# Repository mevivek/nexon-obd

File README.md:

# Obdurate

> *ob·du·rate* — adj. unyielding; refusing to be moved.

**A read-only black box for your car.** It plugs into the OBD-II port and stays
there. It records every drive to onboard flash whether or not a phone is connected,
prints the sample rate it is actually achieving next to every reading, and never
writes anything to the car — which is a test, not a promise: the build fails if a
write service ever appears in the source.

Built on a **Seeed XIAO ESP32S3**. It hosts its own Wi-Fi access point and serves a
gauge dashboard, on-board monitor results, a UDS identifier scanner and browser-based
OTA updates. No app, no account, no internet, no cloud. Join its Wi-Fi and a page
opens; don't, and it keeps recording anyway.

**Developed and verified against a 2022 Tata Nexon 1.2 petrol (BS6).** The transport
layer, ISO-TP, the recorder, the scanner and the honesty rules are generic. The PID
lists (`PID_B1`–`PID_B4`), the ECU addresses (`ID_ECM_REQ`/`ID_TCM_REQ`), the bus
timing and the warning thresholds are that car's — a different one needs those
changed in the source, and there is no porting guide yet. If you try it on another
car, the measurements are the interesting part; open an issue.

[`docs/FINDINGS.md`](docs/FINDINGS.md) is what was measured on this one, including a
catalogue of the ways a cheap ELM327 clone lies to you.

It reaches the car two ways and picks whichever works:

| Transport | Hardware | Speed | Notes |
|---|---|---|---|
| **BLE ELM327** | none — uses a dual-mode ELM327 already in the OBD port | ~2 Hz | Works today |
| **Direct CAN** | SN65HVD230 transceiver (~₹200) | 50–100 Hz | Preferred once wired |

Everything here was verified against the actual vehicle. Where a claim is untested,
it says so.

---

## Quick start

1. Flash the firmware (see [Building](#building)).
2. Power the board — USB, or from the OBD port via a 12 V→5 V buck.
3. Join Wi-Fi **`Obdurate`** / **`changeme1234`**.
4. Open **`http://192.168.4.1`**.

That is the whole install. The dashboard is compiled into the firmware, so flashing
is all it takes — there is no second step, no laptop at the car, and no state where
the board is running but has no page to show.

You can still deploy a bundle to the filesystem with **`web/deploy.sh`**, and it
takes precedence when present. That is the edit loop: changing a line of CSS costs a
22 KB upload rather than a 1.3 MB reflash. The compiled-in copy is the floor
underneath it, so a failed or half-finished deploy falls back to the last dashboard
that was built into the firmware rather than to a stub.

| Page | What it does |
|---|---|
| `/` | Live gauges — RPM, boost, temps, trims, lambda, catalyst, driver demand |
| `/monitors` | Mode 06 on-board monitor test results, with the ECU's own limits |
| `/scan` | Discover — the autopilot, the sweep, triage and the DID watch |
| `/update` | Upload a new `.bin` over Wi-Fi |
| `/dtc` | Stored + pending fault codes as JSON |
| `/data` | Current sample as JSON, plus firmware version and active transport |
| `/trips` | Per-drive CSV logs — list, download, delete |
| `/history` | The stored trend buffer as JSON |
| `/vehicle` | What this car is and which readings it supports, as JSON |
| `/car` | Which car this board is bound to, and whether it is recording |
| `/auto` | The autopilot's phase and progress |
| `/files` | What data is on the filesystem — the list a backup is built from |
| `/file` | One data file, streamed |
| `/reset` | Erase the data, or the data and the dashboard bundle |

The header shows the running firmware version and which transport is actually live
(`can` or `ble`), so a flashed image can be confirmed at a glance.

A poll can come back with only some of its PIDs — the dashboard reads them in three
batched requests, and one batch can time out while the others answer. When that
happens the affected gauges keep showing their last reading, dimmed, and the header
reports `live · holding N`. After 2.5 s without a fresh value they fall back to `—`
rather than showing stale data indefinitely, and a held reading never raises or
sustains a warning — a value from two seconds ago cannot tell you whether the engine
is still overheating.

A single dropped poll is not reported as a fault either — the status only changes to
`no response from ECU` after five consecutive failures. Dropped replies happen, the
values are held through them, and flipping the status on each one reads as a problem
when nothing is wrong.

### Polling runs on the board, not on the page

The board samples the ECU continuously in `loop()`, one batched request per turn,
and `/data` returns the newest cached sample rather than going to the bus. Polling
therefore does not stop when you close the browser, and no request ever waits for a
poll of its own.

It did, however, wait for *someone else's*. The web server is single threaded, and
until v1.8.0 it got exactly one turn per bus exchange — up to 1.2 s on BLE, twice
that when a batch is retried. A tab switch is three requests (the document, `/time`,
and the new page's first poll), so switching pages could sit behind several seconds
of ELM327 timeouts and felt like a page load rather than a page swap.

Two things fix that, both in `bus_yield.h`:

- **The wait loops serve HTTP.** Waiting on the car is otherwise `delay(1)` on BLE
  and a 5 ms blocking receive on CAN. Both now call `webYield()` instead, which
  serves whatever is queued and reports how long it took — and the response deadline
  moves out by exactly that, because the reply is still waiting behind us either way
  (the TWAI RX queue, or the ELM notify buffer). Without the give-back, serving a
  page would eat the ECU's patience window and surface as a phantom timeout. The
  extension is capped at 3 s so one slow handler cannot hold an exchange open.
- **`loop()` drains the queue** instead of taking one request per turn, so a whole
  page load completes in a single turn.

Two guards keep that safe. `WebServer` tracks a single current client, so
`webYield()` refuses to re-enter it from inside a handler; and `obdIsoTp()` sets a
flag for the duration of an exchange so a handler reached from a yield cannot start
a second one underneath a half-finished reassembly. `/dtc` is the only handler that
touches the bus — it stands down when that flag is set, and because it runs inside
`handleClient()` and therefore cannot yield, its own timeouts are kept short.

The pages help too: the shared ~7 KB stylesheet used to be compiled into all five
documents and re-sent on every switch. It is now served once from `/ui.css` with a
version-stamped, immutable URL, and the pages carry an `ETag` so a re-visit is a
304 with no body. That is also worth ~26 KB of flash.

A sample is published after **every** batch, not after all three. The other two are
carried forward from cache while they are still fresh (3 s), so the page updates at
the bus transaction rate rather than a third of it. Batches are not polled equally
either — `b1` carries everything with a sparkline (rpm, speed, MAP, throttle, load,
coolant) and gets half the turns, because oil temperature and battery voltage do not
move fast enough to deserve equal billing:

| | Refresh |
|---|---|
| `b1` — rpm, speed, MAP, throttle, load, coolant | every 3 batches |
| `b4` — pedal, commanded throttle, torque, absolute load | every 3 batches |
| `b2` — oil, IAT, voltage, trims, fuel rate | every 6 batches |
| `b3` — lambda, catalyst, timing, run time, ambient, fuel | every 6 batches |

A batch that has not answered for three of its own polling cycles is dropped to
`null` rather than published as current, so carrying values forward can never
present a stale number as live. That window is measured, not fixed: `b2` and `b3`
come round once every four batches, so a flat timeout only holds if a batch
completes quickly. Over BLE it does not, and those two batches then expire before
their next turn — blanking twelve of the twenty rows in **All values** on every
cycle. The dashboard's own hold window scales the same way, off the observed sample
interval.

The `[alive]` serial line prints `batch=`, `cycle=` and `stale=` so all three are
visible rather than inferred.

### The board says how fast it is actually reading the car

Those numbers used to go only to the serial log, where nobody sitting in a car can
read them. They are now in `/data` as a `q` block, and on the page as the muted
trailer next to the status pill:

```
live · holding 2      1.87 Hz · b3 6.8 s
```

The rate quoted is **the board's**, not the page's. The page's fetch loop is capped
by its poll interval and throttled harder still in a backgrounded tab, so a rate
measured there can only ever be at or below the one the board is publishing — it
would understate a healthy link and could never catch a sick one. Where the two
genuinely disagree, both are shown, because that is the case worth knowing about:
the log holds samples the screen is not showing you.

This is the number every tool in this category leaves out. An ELM327 round trip puts
a cheap clone somewhere near five PIDs a second; set a tenth-of-a-second logging
interval against that and you get a log that looks complete and is mostly the
previous row repeated, with nothing anywhere to tell you which it is.

Two rules keep it honest, and they are the same ones the readings themselves follow:

- **`hz` is null, not zero, until a full pass has been timed.** A rate of zero is a
  claim that the bus is dead. Not having measured one yet is not that claim, and the
  first second of every drive is spent in that state.
- **A batch that has never answered is null, not a very large age.** Never-answered
  is usually a PID this ECU does not support; long-ago-answered is a link going bad.
  Collapsing them presents the first as the second.

The stalest batch is named only once it is past the board's own derived staleness
window — `b2` and `b3` come round once every four turns by design, so reporting the
worst one unconditionally would be a permanent complaint about nothing.

`/data` also carries a `boot` block: how this run started (`power`, `wake`, `panic`,
`brownout`, `wdt`, …), how long it has been going, and how many deep-sleep wakes
since the last cold boot. A recorder that runs unattended has to be able to answer
*what happened while I was not looking* — a board that has quietly panicked and
restarted forty times otherwise looks exactly like one that has been up all week.

**On BLE, the bus transaction rate is the limit**, and it is mostly round-trip
latency rather than the ECU. The connection interval is the floor: at a default of
40–50 ms a request and its reply cannot beat about a tenth of a second however fast
the car answers. The firmware asks for 7.5–15 ms and a 247-byte MTU, which collapses
a ~80-character reply from four or five notifications into one or two. The adapter
may refuse either, in which case nothing is worse than before. The serial log prints
`batch=NNNms` so the real cost is visible rather than guessed at.

The dashboard stops requesting while the page is off screen, and the Hz readout
counts *published samples* rather than fetches — the same cached sample can be
fetched several times and must not inflate the rate.

### Mileage

Two figures, in the glance area under boost and coolant:

- **Mileage** — the average over this drive, with the totals it came from
  (`23.6 km · 1.66 L`) underneath so the number can be checked rather than trusted.
- **Right now** — instantaneous km/L, which is what the pedal moves. Standing still
  it reads `—` and says `idling` instead, because speed ÷ nothing is not a mileage.

There is no PID for fuel economy, so it is integrated on the board from speed
(`0D`) and fuel rate (`5E`), both confirmed supported on this ECU. On the board and
not on the page, so locking the phone or closing the browser does not lose the drive.
Two rules keep it honest:

- **Both inputs or neither.** Fuel rate lives in the `b2` batch and refreshes half as
  often as speed, so it goes absent regularly. Counting the distance anyway would
  divide real kilometres by an understated litre count and report a mileage better
  than the car achieved.
- **Gaps are not driving.** An interval longer than 5 s — a BLE dropout, a scan taking
  the bus, a wake from sleep — is skipped rather than integrated at the last known
  speed. The clock still moves, so the interval after an outage is one interval, not
  the whole outage.

The average is withheld until roughly the first 0.5 km and 0.1 L. Before that it
swings by tens of km/L between polls and reads as a broken gauge.

Totals start at zero each time the board powers up, which — given the
accessory-socket supply — is exactly one drive. They also go into the trip CSV as
`trip_km` and `trip_l`, so economy over any stretch of a drive can be recovered by
differencing two rows.

One caveat worth knowing: `5E` is the ECU's injection model, not a flow meter. Trip
km/L from it typically reads a few percent optimistic against tank-to-tank. It is
excellent for comparing drives and weaker as an absolute.

### Driver demand vs. delivery

Six of the 55 PIDs the ECM supports trace one chain: **accelerator pedal (`49`/`4A`)
→ commanded throttle (`4C`) → actual throttle (`11`) → demanded torque (`61`) →
delivered torque (`62`)**, with absolute load (`43`) alongside. That is what you
asked the car for, what the ECU decided to do about it, and what the engine actually
produced — which on a small turbo is the interesting part.

Torque is reported as a percentage of the engine's reference torque (`63`), a
constant read once at startup like barometric pressure, so the newton-metre figures
are derived rather than read.

> The scalings are the J1979 ones and have **not been verified against this car** —
> `FINDINGS.md` lists the torque PID scaling as an open question precisely because it
> needs data under load. A wrong data *length* is caught (`mode01Walk` rejects the
> batch), but a wrong *scaling* would not be. Treat the numbers as provisional until
> they have been watched under load and found sane.

### On-board monitors (mode 06)

Mode 06 is the ECU's own test results: what each monitor measured, and the limits it
is judged against. `FINDINGS.md` recorded it as supported (`46 00 C0000001`) and
never explored — so `/monitors` reads it.

The value of it over `/dtc` is that a fault code only appears once a system has
already failed. Mode 06 shows how much room is left, so a catalyst drifting toward
its threshold is visible while it is still passing.

**Pass and headroom do not require knowing the units.** A test passes when its value
sits inside its own limits, and the headroom is a fraction of that window — both
unit-free. The unit-and-scaling table is long and only partly documented, so values
are shown raw with their scaling id, decoded only where the multiplier is
unambiguous. Monitor names likewise: only unambiguous J1979 ids are named, the rest
keep their raw id rather than being given a label that might be wrong.

Discovery walks the support masks (`00` → `20` → `40` …, each mask's last bit
pointing at the next), then each monitor is read one at a time. It runs only while
the page is open — monitors move over minutes, and polling them continuously would
take bus time from the values that move now.

### The DID scan runs in the background

A scan is driven by the board, so it continues if you navigate away, close the
browser, or lock the phone. Only **Stop** — or an OTA upload, which never flashes
mid-scan — ends it.

While it runs the scanner takes most of the bus, but not all of it — the sampler
still gets one batch every two seconds, so live values keep moving slowly rather
than freezing. That costs roughly 15 % of scan throughput, which is a good trade
against a dashboard that is dead for the length of a sweep.

The Live page shows the sweep's progress with counts as well as a percentage — a
full pass is 65,536 requests, so a percentage alone rounds to zero for a long time
and reads as stuck — and the scanner page estimates the time remaining.

Scanning is time-boxed to 250 ms per turn rather than a fixed identifier count. A
count behaves wildly differently per transport — 40 identifiers is about a second on
CAN but roughly 22 s over BLE, during which nothing answers the web server and the
board appears hung.

### Watching identifiers to find out what they hold

A sweep finds identifiers that answer. It cannot say what any of them contain — the
manufacturer-specific block (ISO 14229-1 hands `0100`–`A5FF` to the manufacturer)
comes back as one or two raw bytes with no name, unit or scaling, and that lives in
an ODX database nobody outside the supplier has.

What you can do is correlate. `/watch` reads up to **8** chosen identifiers
continuously and shows them next to rpm, speed, coolant, intake, load and throttle,
each with a sparkline. Blip the throttle and an rpm-linked value gives itself away.
The ones the scanner found are offered as checkboxes, so there is no copying hex
between pages.

**Coming from a build before 1.7.0:** those sweeps kept their hits in RAM only —
nothing was written to flash — so an updated board comes up with an empty picker
even though the sweep happened. The `did_hits.csv` you exported is the only copy,
and the picker loads it directly: choose the file and the identifiers appear as
checkboxes, merged with anything the board found itself. It is parsed in the
browser and kept in `localStorage`; nothing is uploaded, and there is no endpoint
that would make a browser a second source of truth for what the board found.

The same readings become extra columns on the trip CSV — two per identifier: the
bytes decoded big-endian, and the raw bytes beside them. Two bytes might equally be
one 16-bit value or two 8-bit ones and nothing in the reply says which, so the
decode is a convenience and the raw column is the record. An identifier that has
stopped answering writes **empty** cells rather than zeros, the same rule the PID
columns already follow: a missing reading must not correlate as a value of nought.

Changing the set **rotates the CSV**. Columns are fixed when a file is opened, and
shifting them halfway down one is worse than having two files. Re-applying an
identical set is not a change, so pressing Apply twice does not litter the partition.

The cost is real and the page states it. Every watched identifier is one more bus
exchange, and BLE affords about six a second in total — eight at the default one per
second is roughly a sixth of the budget. Watching **pauses entirely while a sweep is
running**; a sweep is already hours long and shares the bus with the sampler, and a
third claimant would do both jobs badly.

This gives correlation, not meaning. It will tell you `1002` tracks coolant; the
offset and scale come from fitting the logged column against the PID afterwards.
Service `0x22` is still a read — only the identifier varies, never the service.

### Trip logs

A CSV row a second while the ECU is answering, written to the 1.5 MB filesystem
partition. Twenty-six columns — wall-clock time and uptime, then twenty-four
readings — and empty cells rather than zeros where a value was not read, so a gap is
a gap and not a reading of nought.

> **This did not work until v1.12.0.** `tripTick()` was written, documented here,
> and never called from anywhere. `/trips/list` returned an empty array on every
> board that has ever run this firmware, and the DID-correlation workflow described
> below — the route this project has for decoding the `10xx` block — has never
> produced a row. If you flashed anything before v1.12.0, there are no trip logs to
> recover; there never were any.

Roughly half a megabyte an hour bare, so the partition holds two to three hours, and
the oldest trip is deleted automatically when space runs short. Watched identifiers
change that materially: each one adds two columns and up to 26 bytes to every row,
so a full set of eight is closer to **1.3 MB an hour — about one hour of capacity**.
The columns are chosen when a file is opened, so the cost is fixed for that file.

LittleFS rather than SPIFFS: the board loses power the instant the ignition goes
off, mid-write as often as not, and LittleFS is built to survive exactly that.

A full partition is the ordinary end state of a device left in a car, not an edge
case. Logging stops rather than pretending: `tripEnsureSpace()` reports whether it
managed to reach the free-space floor, a file is not opened when it did not, and the
row terminator is checked so a write that did not land is seen. Without those, a
failed write left `size()` where it was, the rotation that would have freed space
never fired again, and logging stopped for the rest of the drive in silence.

The clock comes from whichever page you open, so a drive that starts before you open
one has an unset clock for its first rows. Each file's header records whether the
clock was set rather than implying a timestamp it does not have.

### Scans survive being switched off

A sweep is tens of thousands of requests — the better part of a day over BLE — so it
has to outlast the car being switched off. Position goes to NVS as it runs, hits are
appended to the filesystem the moment they are found, and an interrupted sweep
resumes on the next boot rather than starting over.

It also stops sweeping when the ECU stops answering. **A timeout and a negative
response mean opposite things:** a negative response is the ECU saying "no such
identifier", which is a result worth recording; a timeout is no answer at all. After
25 consecutive timeouts the sweep holds its position and probes every few seconds
until the car answers again.

Without that, switching the ignition off mid-sweep would record thousands of
identifiers as "no response" — turning an unswept range into one that looks swept
and empty. That is the same class of silent wrong answer as the `ATCRA` bug in
[FINDINGS](docs/FINDINGS.md), and it matters here because the whole value of the
sweep is its negative result.

### Trend history

The board keeps one hour of RPM, speed, boost and coolant at 6-second resolution and
serves it at `/history`, so the sparklines have shape the moment the page loads
instead of starting flat.

It survives restarts, which matters more than it sounds — the board restarts
constantly in normal use, so history in ordinary RAM would be wiped every time you
got back in the car. How it restarts depends on how it is powered: from the
accessory socket the power is simply cut when the car goes off; from the
permanently-live OBD pin 16 it deep-sleeps after 10 idle minutes and wakes every
30 s, running `setup()` each time.

| Store | Survives | Written |
|---|---|---|
| RTC slow memory (4.8 KB) | deep sleep | every 6 s, free |
| NVS (flash) | power loss | every 6 s (each new sample), and before sleeping |

Which store matters depends on how the board is powered. Wired to the ignition it
simply loses power when the car goes off — RTC memory does not survive that, and the
save on the way into deep sleep never runs, so the periodic flash write is the only
thing keeping a trip's history. It runs on every new sample, so switching off costs
at most 6 seconds. Wired to the permanently-live pin 16 the board deep-sleeps
instead, and RTC memory carries the buffer across for free.

Flushing that often is only affordable because a flush writes **the 400-byte chunk
that moved**, not the whole 4800-byte ring. Rewriting all of it — which is what it
did until v1.3.0 — costs somewhere over a flash sector erase per save, so shortening
the interval that way would have burned through NVS endurance in a couple of years.
Chunked, ten times the flush rate still churns less flash than the old
sixty-second full-buffer write did.

### What car is this

Every other part of this firmware is written against one vehicle. The PID batches
are the set a Nexon replies to, the DID register is 214 verdicts about a Nexon's
ECU, and the dashboard draws tiles for readings that car publishes. Plugged into
anything else, none of that announces itself — the tiles that cannot be filled read
blank, which is indistinguishable from a car that is simply not answering yet.

So the board asks, once per boot: the mode 01 support bitmaps block by block, then
mode 09 for the VIN, the calibration id and its checksum, then one probe at the
transmission's responder id. `/vehicle` reports the answers, including which of the
PIDs the sampler actually polls this car supports.

This is **discovery, not adaptation**. The sampler still asks for the same PID set
and an unsupported reading still comes back absent — it is now labelled
absent-because-unsupported rather than absent-because-silent, which is the whole
difference between a dashboard that is broken and one that is honest. Adapting the
batches at runtime needs a vehicle-profile format, and designing that against a
sample of one car would be designing it blind.

Three states throughout, never two. A support block whose bitmap never arrived reads
*unknown*, not *no*; a mode 09 refusal is a fact about the car, a timeout is a fact
about the last few seconds. Nothing answering at the second responder id is reported
as exactly that, never as "no second ECU" — a module that is not fitted and one that
is not awake produce the same nothing on a CAN bus.

### Backup, restore, and the check in between

A sweep is over half an hour on CAN and the better part of a day over BLE, the
register behind it takes drives to build, and the trip logs are the drives
themselves. All of it lives on a 1.5 MB partition inside a device that gets
unplugged, reflashed and left in a hot car.

The Board page takes the lot off as a ZIP, puts it back, and clears it. The archive
is assembled **in the browser** — the board has one core and a car to poll while it
serves you, so it offers a list (`/files`), a reader (`/file`) and a writer
(`/file/put`) and the page does the work. Entries are STORED, never deflated, so the
file opens with any unzip tool and the reader that puts it back is a header walk
rather than an inflater shipped into a 300 KB budget.

The reason any of this needs the section above: `didmap.csv` is 214 verdicts about
one specific engine and nothing inside it says which. Restored onto a different car
it would not fail — it would attach, silently, and every conclusion drawn from it
afterwards would be about the wrong engine. So a backup carries a manifest holding a
hash of the VIN and calibration id, and a restore compares it. A mismatch is refused
outright with no way past it. A backup or a board with no identity at all is the
ordinary state of a car that has not been driven yet, and that is put to the person
as a question rather than answered on their behalf.

The manifest carries the hash, not the VIN. It answers the only question the archive
is asked exactly as well, and a backup is a file that gets copied to a phone and a
laptop.

### One board, one car

Everything this board accumulates is about a particular vehicle — the sweep's hits
are that car's identifier space, the register is verdicts about that car's ECU, the
trip logs are that car's drives. None of it carries a vehicle in the record itself,
so mixing two cars does not produce a detectable error. It produces a file that is
quietly wrong forever.

So the binding is explicit. The board stores the key of the car it belongs to, and
in a car that is **provably** a different one it records nothing: no sweep, no
triage, no trip log, no correlation. The live dashboard keeps working, because it
reads what the car is doing now and persists none of it — and a board showing a
blank screen in the wrong car would be useless at exactly the moment somebody wants
to glance at a temperature. It also bounds the filesystem, which is the other half
of the reason: a 1.5 MB partition holding one car's data is comfortable and two
cars' is not.

A banner then offers the only choice that is anyone's to make: **onboard this car**,
which erases the previous one's data and starts again, or **keep the other car**,
which leaves the binding alone and gives this one live readings only.

Three answers, not two, and the middle one is the important one. A key exists only
once mode 09 has answered, so "the keys differ" and "there is no key" are completely
different facts and only the first stops anything. Reading absence as a mismatch
would silently disable recording on every car that declines mode 09, and the
symptom — a board that runs, shows live data and never writes a trip log — is one
nobody would diagnose.

### The autopilot

The investigation used to be four phases and three decisions, hours apart, with the
last step done by hand in a spreadsheet. Nobody chooses differently at any of those
points, which is what makes it automatable — and the phases outlast anyone's
attention, so a prompt between them is one that gets missed.

Started once, the board sweeps the identifier space, triages the hits to find which
move, then watches the ones that move eight at a time, fitting each against the live
readings. It advances on its own and keeps its phase in NVS, because the ignition
going off is a power cut and this pipeline is measured in drives:

- **Sweep** — about 30 minutes on CAN, the better part of a day over BLE.
- **Sweep (TCM)** — the same again at the transmission controller, which is a
  separate identifier space at a separate address. Only when discovery's probe at
  0x7E9 actually answered: a sweep of an ECU that is not there does not fail, it
  stalls, and holding position — right for a sweep — would hold the pipeline for
  good. Silence there is reported as "not swept, and here is why", never as proof
  there is no module.
- **Triage** — about an hour of engine-on. This adapter answers roughly half of what
  it is asked, so ten clean reads of every hit needs about twenty passes.
- **Watch** — one drive per eight identifiers, so eight or nine drives for a
  register the size of this car's.

The watch set rotates between drives and never during one: changing it bumps the
watch generation, which rotates the trip CSV, and rotating mid-drive would turn one
drive into a pile of short files.

Two things it will not do. A sweep that finds nothing is a **conclusion** — this ECU
does not answer service 0x22 — not a reason to sweep again. And a car the board is
not bound to **holds** the pipeline rather than ending it, so an afternoon in
somebody else's car does not cost the drives already spent.

### The board does the fitting now

Watching logs an identifier beside rpm and coolant; something then has to fit one
against the other. That was the only step still done by a person, it is the same
arithmetic every time, and it is why a board that had collected everything needed to
answer "what is 1002" still could not say anything about it.

A Pearson correlation is six running sums. Eight watched identifiers against six
reference signals is forty-eight of them, which is nothing on an ESP32, and the best
fit goes into the register as three new columns — so `/didmap.csv` now carries
`tracks,r,samples` on the end. They are appended rather than inserted so a register
written by an older firmware still loads; that file is what a restore puts back, and
a format that rejected last month's backup would throw away hours of bus time to
gain a column.

**It says "tracks", never "is".** Everything under a bonnet correlates with
everything else — oil temperature tracks coolant almost perfectly, and both track
runtime after a cold start — so a strong fit narrows the field rather than settling
it. r is also unchanged by offset and scale, so a perfect correlation still leaves
the units unknown. Naming an identifier stays a human act, which is why
`DID_IDENTIFIED` outranks every machine verdict.

A pair is only counted when **both** sides are present. This adapter drops roughly
half of what it is asked, and folding a missing reply in as a zero would fit the
dropout pattern rather than the car — convincingly.

### Being left in the car

The board deep-sleeps after ten minutes with no ECU response. That timer answers
*the car is off*, which is the ordinary case, and it does not answer *the battery is
going flat* — the two come apart exactly where it matters. An ECU that keeps
answering with the engine stopped (ignition on at the roadside, a long session
parked, a module that stays awake) resets the idle timer on every reply, so the
ten-minute guard never arms and the board keeps drawing from a battery nothing is
charging.

So there is a second floor under it: **below 11.8 V for thirty continuous seconds
with the engine stopped, the board shuts down.** A lead-acid battery at rest sits
near 12.6 V; 11.8 V is roughly a quarter charged and about where a cold start stops
being a certainty.

Three things keep it from firing when it should not, and each is tested:

- **Cranking does not trip it.** The rail sits at nine volts and below for about a
  second while the starter turns, which is the one moment the reading is low and
  switching off would be exactly wrong. Thirty continuous seconds is well past any
  crank, and past the sag from a fan or a heated screen starting up.
- **A turning engine is proof something is charging**, whatever the rail reads, so
  any rpm above 300 breaks the run outright.
- **An absent reading is never a low reading.** An unread voltage and an unknown
  engine state both break the run rather than counting toward it, and the guard is
  fed the sample only while it is fresh — a voltage from ten minutes ago must not
  switch the board off now. That is the idle timer's job and it is already running.

> **The idle draw has not been measured.** The guard above bounds the worst case at
> a battery that can still start the car, but no number for what this board actually
> pulls — asleep, or awake with the AP up — has been put on a meter yet. Until it
> has, treat the advice below about unplugging a parked car as applying to the board
> as much as to the adapter.

The onboard LED encodes state, which matters when the board is hidden under the dash:

- **slow blink (1 Hz)** — alive, Wi-Fi up, ECU not answering
- **fast blink (5 Hz)** — talking to the ECU
- **double-blink** — DID scan running

---

## Frontend

The dashboard is a Preact app under `web/`, built with Vite and served off the
board's filesystem. It is not compiled into the firmware.

```bash
npm --prefix web install
npm --prefix web test          # 206 checks
web/deploy.sh                  # build, then upload to 192.168.4.1
```

**It ships two ways, and the order matters.** The built bundle is compiled into the
firmware, so flashing the board is the whole install. A bundle uploaded to LittleFS
overrides it, which is what keeps the edit loop cheap: changing a line of CSS costs a
27 KB upload, not a 1.3 MB reflash.

That is not a return to what v1.11.0 removed. What went then was hand-written
JavaScript inside C++ raw string literals — no bundler, no packages, no source maps,
and nothing in the build that ever parsed it, so a typo shipped and surfaced as a
dead dashboard in the car. All of that stays gone. `web/scripts/embed.mjs` reads the
output of the ordinary Vite build, after the ordinary Vitest suite, and turns the
finished gzipped bytes into a byte array. Nothing about how the frontend is written,
bundled or tested changes — only where a copy of the result ends up.

What it buys is that there is no state where the board runs and has no page. Someone
who flashes through [`docs/flash/`](docs/flash/) has a working dashboard the moment
it boots, rather than needing a laptop, the board's Wi-Fi and `web/deploy.sh` first.

**Why the board and not a web host.** The access point has no internet, so a phone
joined to it cannot load a page from anywhere else. Chrome 142 relaxed mixed-content
checks for literal private IPs behind a permission prompt, so an HTTPS page *can*
now reach `192.168.4.1` — but only on Chrome, only if the permission was granted
before you got in the car, and Android 17 adds a second prompt on top. Serving from
the board has none of those conditions: no mixed content, no CORS, no permissions, no
internet, any browser.

**Deploying cannot brick it**, and the floor is higher than it was. `/ui` is compiled
into flash, so the page that fixes a bad deploy never depends on the deploy having
worked. If no bundle is installed, or the upload was interrupted, `/` falls back to
the dashboard compiled into the firmware — the whole thing, not a four-value stub.
Trip logging, the DID sweep and the history buffer are the board's work and run
regardless of what the browser can see.

| | |
|---|---|
| Bundle | 27 KB gzipped, **one file**, compiled in and overridable |
| Budget | 300 KB, capped in the build and enforced by the firmware on upload |
| Shares with | trip logs — 300 KB is about 35 minutes of recording capacity |

The build inlines the script and stylesheet into `index.html`, so a deploy is a
single `index.html.gz`. That is not for the bytes — one gzip stream over the lot is
barely smaller than three — but for how it gets installed: the board is updated from
a phone standing next to a car, and a firmware update is one `.bin`, so the frontend
should cost no more than that.

The firmware serves it with `Content-Encoding: gzip` and `no-cache`, so a new deploy
is always picked up, and answers `/monitors`, `/trips`, `/watch` and `/scan` as
redirects into the app's routes so old bookmarks keep working.

**The `/data` contract** is declared in `contract/data.json` and checked from both
ends — the firmware test asserts it against `handleData()` in both directions, so a
field renamed on one side fails the build instead of blanking a gauge on the road.

---

## Hardware

### Option A — no extra parts

Uses a dual-mode ELM327 clone over **BLE GATT**. The ESP32-S3 has **no Bluetooth Classic
radio**, so it cannot use the usual SPP path — but many ELM327 clones also expose a BLE
interface, and this firmware drives that.

Check yours advertises service `FFF0`. On the unit this was built against:

```
BLE address 81:23:45:67:89:BA   name "OBDBLE"
  SERVICE 0000fff0
    CHAR 0000fff1  Read, Notify               <- responses
    CHAR 0000fff2  WriteWithoutResponse, Write <- commands
```

Note the BLE address is the Classic MAC with the top bit of octet 0 set
(`01:…` → `81:…`). Set `ELM_BLE_ADDR` in `elm_ble.h` to match your adapter.

### Option B — direct CAN (recommended)

| Part | Notes |
|---|---|
| **SN65HVD230** transceiver | **3.3 V part.** Do *not* use TJA1050 or MCP2551 — they are 5 V logic and will damage the ESP32's RX pin |
| 12 V→5 V buck (MP1584/LM2596) | Set output to 5 V *before* connecting the board |
| OBD-II male pigtail | |

**Wiring**

| XIAO ESP32S3 | SN65HVD230 |
|---|---|
| D1 (GPIO2) | CTX / D |
| D2 (GPIO3) | CRX / R |
| 3V3 | VCC |
| GND | GND |

| SN65HVD230 | OBD-II pin |
|---|---|
| CANH | 6 |
| CANL | 14 |

Power from OBD pin 16 (+12 V) and pin 4/5 (GND) into the buck, 5 V out to the XIAO's `5V` pad.

> **Remove the 120 Ω termination resistor** on the transceiver breakout. The vehicle bus
> is already terminated at both ends; a third terminator causes bus errors.

> **OBD pin 16 is permanently live**, so anything plugged into the OBD port draws
> from the battery whether the car is running or not. That includes a BLE ELM327
> adapter — clones typically pull 20–50 mA, roughly 0.5–1 Ah a day — so unplug the
> adapter if the car is parked for more than a few days. This applies to the adapter
> even when the board itself is powered from the accessory socket and switches off
> with the ignition; the two are independent.
>
> The board deep-sleeps after 10 minutes with no ECU response, which protects the
> battery only if the board is itself wired to a permanently-live supply.

---

## Building

```bash
firmware/build.sh              # tests, then compile
firmware/build.sh --upload     # …then flash over USB (PORT=… to pick the port)
```

If you already have `arduino-cli` with the ESP32 core — an Arduino IDE install counts
— it uses that and downloads nothing. Only on a machine with neither does it install a
private copy into `firmware/.toolchain/` (~6 GB unpacked, several minutes), and that
install writes nothing outside the repo, so deleting the directory undoes it
completely. `OBDURATE_ISOLATED=1` forces the private toolchain, which is what CI
wants: a build that depends on whatever happens to be on the machine is not
reproducible.

The upload port is guessed from `arduino-cli board list`, taking only a port it
recognises as an ESP32 — Windows has several Bluetooth serial ports that must not be
flashed at. Override with `PORT=COM3` or `PORT=/dev/ttyACM0`.

> Building needs `g++`, `python3` and `node` on `PATH` for the host tests, which run
> before the compile. Contributor notes for the development machine — including where
> its compiler lives and how to read the board's serial log on Windows — are in
> [`CLAUDE.md`](CLAUDE.md).

The output you want is **`firmware/build/Obdurate-v<version>.bin`** — the app image,
which is what `/update` takes. The version comes from
[`firmware/Obdurate/version.h`](firmware/Obdurate/version.h); bump it there and the
filename, the dashboard header and the serial banner all follow.
`Obdurate.ino.merged.bin` in the same directory is a full-flash image for USB
recovery; feeding *that* to `/update` will not work.

By hand, if you would rather not use the script:

```bash
arduino-cli config add board_manager.additional_urls \
  https://espressif.github.io/arduino-esp32/package_esp32_index.json
arduino-cli core update-index
arduino-cli core install esp32:esp32

arduino-cli compile --fqbn esp32:esp32:XIAO_ESP32S3 --output-dir build firmware/Obdurate
arduino-cli upload -p COM3 --fqbn esp32:esp32:XIAO_ESP32S3 firmware/Obdurate
```

Current size: **1.26 MB flash (37 % of `app0`)**, 49 KB RAM (15 %), plus 4.8 KB of
RTC slow memory for the trend buffer. The frontend is no longer part of that: it is
a 22 KB gzipped bundle on the filesystem, and moving it out returned 47 KB of flash.

The default `default_8MB` partition already provides `ota_0` + `ota_1` at 3.19 MB each,
so OTA works without changing the partition scheme.

### Tests

```bash
firmware/test/run.sh          # needs g++, python3 and node — no ESP32 core, no board
```

The ISO-TP layer and the mode-01 batch poller are extracted straight out of
`Obdurate.ino` and compiled against fake TWAI and ELM327 shims, so frame sequences
that are impractical to stage against a real car — a dropped consecutive frame, a
reordered sequence number, a reply that stops halfway — are covered. The same shims
stand in for the web server, so the deadline give-back described above is tested for
the two properties that make it safe: a silent ECU is still reported silent, and the
extension is bounded. Everything else the sketch
can be asked about without a board — the `/data` contract, the routing, the caching
headers, the DID watch wiring, the trip columns, the history constants — is asserted
against the source under node.

The frontend has its own suite, `npm --prefix web test`: 382 checks over the
hold-last-value merge, the warning-flag gating, the rate tracker, the mileage
readouts and each page's logic, run against the modules that implement them. That is
the point of the split — those used to be JavaScript inside C++ raw string literals,
which nothing in the build ever parsed, so a typo shipped and surfaced as a dead
dashboard in the car.

The "All values" table is checked in a real browser instead, because the node
harness structurally cannot check it: its fake DOM creates any element asked for by
id, so a table whose cells are built once and then addressed by id passes whether or
not those ids line up with the rows — the whole suite goes green with every value
shown against the wrong PID. `test_table.mjs` renders the built bundle and
the built bundle, drives it through a full sample, a partial poll and a recovery,
and asserts that row *i* shows the value of the PID row *i* names. It skips itself, without failing, where
Playwright is not installed.

To look at the pages without flashing anything:

```bash
node firmware/test/shots.mjs out/     # needs playwright + chromium
```

It serves the real pages against a mock `/data` and screenshots them at phone and
tablet widths across four states — cruising, a partial poll, warnings, and ignition
off. The partial-poll shot is the one worth checking after any change to the polling
code, since that is the state that used to blank the dashboard.

### OTA

Run `firmware/build.sh`, join `Obdurate`, and upload
`firmware/build/Obdurate-v<version>.bin` at `http://192.168.4.1/update`. The header
shows the new version once it reboots, which is how you confirm the flash took.

The board runs from `app0`; an upload streams into `app1`; `otadata` only flips once
`Update.end()` verifies the image, then it reboots. An interrupted or corrupt upload never
touches `otadata`, so **a failed OTA cannot brick the board** — it reboots into the
firmware it was already running.

So the loop is: build locally → copy the `.bin` to your phone → join the board's Wi-Fi →
upload at `/update`. No dev machine needed at the car, only to produce the image.

> **CI is not in use.** [`ci/build.yml`](ci/build.yml) is kept current — it runs the host
> tests and compiles the firmware — but it is parked outside `.github/workflows/`, since
> pushing there needs the `workflow` OAuth scope this repo's token lacks. Build locally
> with `firmware/build.sh`. To enable CI later:
>
> ```bash
> gh auth refresh -h github.com -s workflow
> git mv ci/build.yml .github/workflows/build.yml
> git commit -m "Enable CI" && git push
> ```

---

## Before you use this

Change the access point credentials in `Obdurate.ino` — they are placeholders, and the
board is an open target on any network it creates:

```cpp
static const char *AP_SSID = "Obdurate";
static const char *AP_PASS = "changeme1234";   // >= 8 chars
```

`/update` has **no authentication**. Anyone who can join the AP can flash the board, so a
strong `AP_PASS` is the only thing protecting it.

Set `ELM_BLE_ADDR` in `elm_ble.h` to your own adapter's BLE address — the one committed
here is from the unit this was developed against.

---

## Architecture

```
                    ┌───────────────────────────┐
  phone ──Wi-Fi AP──┤  XIAO ESP32S3             │
                    │   WebServer :80           │
                    │   bundle (LittleFS) + API │
                    │                           │
                    │   obdIsoTp() dispatcher   │
                    │      ├── canIsoTp  (TWAI) ├──SN65HVD230──┐
                    │      └── bleIsoTp  (GATT) ├──BLE──ELM327─┤ OBD-II
                    └───────────────────────────┘              │  pins 6/14
                                                               ▼
                                                            vehicle CAN
```

Both transports implement the same contract — request bytes in, reassembled ISO-TP
payload out — so mode 01, mode 03 and UDS `0x22` are written once and work on either.

`chooseTransport()` prefers CAN when the transceiver answers, else falls back to BLE.
While the ECU is silent it re-evaluates on a backoff — 2 s, then 4, 8, 16, settling
at 20 — resetting to impatient as soon as data arrives.

That matters when the adapter outlives the board, which is the usual split: the OBD
port is always live but an accessory-socket supply is not. Every start then meets an
ELM327 that may still be holding the BLE link to a board that vanished without
disconnecting, so the first connect can fail for a reason that clears itself within
seconds. A flat retry interval meant a dead dashboard for that whole interval at
every ignition.

---

## Safety

This firmware is **read-only by design**, and since v1.12.0 that is a test rather
than a promise. Every request buffer in the sketch is found from its call sites, its
service byte read out of the source, and checked against the list of reads. Adding a
write service fails the build and names it.

What it actually sends, as the check reports it:

| Service | |
|---|---|
| `0x01` | mode 01 live data |
| `0x03` | mode 03 stored fault codes |
| `0x06` | mode 06 on-board monitor results |
| `0x22` | UDS ReadDataByIdentifier |

plus ISO-TP flow control. It never sends:

| Service | Why not |
|---|---|
| `0x2E` WriteDataByIdentifier | writes ECU memory |
| `0x31` RoutineControl | triggers actuators |
| `0x11` ECUReset | resets a live ECU |
| `0x10` DiagnosticSessionControl | changes ECU state |
| `0x27` SecurityAccess | unlocks protected functions |
| `0x14` ClearDiagnosticInformation | erases the car's own record |

> This table used to claim mode 07 (pending codes) and mode 09 (vehicle info) as
> well. Neither is sent — there is no `0x07` or `0x09` request anywhere in the
> sketch, and the sketch's own header comment made the same claim. Writing the check
> is what found it. Both are reads and both are worth having; they are simply not
> implemented yet.

A request is also bounded now. An ISO-TP single frame is one PCI byte and seven of
payload, and the request was copied into an eight-byte stack buffer with nothing
checking the length. The largest caller in the tree — the mode 01 batch, six PIDs
plus the mode byte — passes exactly seven. At the limit, with nothing spare: a
seventh PID in a batch, or packing two identifiers into one `0x22` request to get
the obvious threefold throughput win, would have written past the frame and said
nothing about it.

Run scans **parked**. Reading is safe; a stalled request while driving is not worth the risk.

---

## Documentation

- **[docs/FINDINGS.md](docs/FINDINGS.md)** — what this specific car exposes, and the
  adapter quirks that cost hours to discover
- **[docs/TOOLS.md](docs/TOOLS.md)** — the PowerShell scripts in `tools/`

## Licence

MIT — see [LICENSE](LICENSE).

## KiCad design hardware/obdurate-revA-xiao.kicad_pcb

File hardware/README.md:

# Obdurate Rev A — hardware

One carrier board, 40 × 40 mm, four layers, in a clear Minitools case whose
OBD-II connector is a matched module from the same family. It carries the CAN
transceiver, the 12 V power chain and the test points; the MCU arrives as a
module, and there are **two variants of which module**.

**There is no schematic or layout here yet, and no Gerbers.** What is here is
everything a schematic would carry, in formats that can be checked: the netlist,
the placement, the board outline, the bill of materials and the fab settings.

Everything is a *design*, not a *measurement*. Nothing has been fabricated. The
prototype that proved the firmware is a XIAO ESP32S3 on flying leads to an
SN65HVD230 breakout — which is exactly what the `-xiao` variant turns into a board.

---

## Two variants, one circuit

| | `-xiao` | `-wroom` |
|---|---|---|
| Module | Seeed XIAO ESP32S3, 21 × 17.5 mm | ESP32-S3-WROOM-1-N8R8, 18 × 25.5 mm |
| Buck output | **5 V** into the XIAO's 5V pad; its LDO makes 3.3 V | **3.3 V** directly |
| USB | on the module | J2 on the board, **0.5 mm pitch** |
| 3.3 V regulator | on the module | U4 + D3 OR diode on the board |
| Status LED | **on the module** — its onboard LED *is* GPIO21 | LED1 + R1 on the board |
| Boot / reset | buttons on the module | R3, R4, C7 on the board |
| Antenna | U.FL flying part, positioned in the case | PCB antenna, needs a board keepout |
| Finest pitch | 1.27 mm (SOIC-8) | 0.5 mm (USB-C) |
| Parts | ~25 | ~38 |
| Module cost | ~$7.00 | $3.20 |

**Rev A is `-xiao`.** Rev A's job is Gate 1 — five units surviving a week in a
car — not hitting a cost target, and the XIAO removes twelve parts, the finest
pitch on the board, the antenna keepout and two open questions. It is also what
the firmware already runs on, so nothing about the software is new.

**`-wroom` is the volume answer.** Roughly $2.70 a unit cheaper once the twelve
parts it adds back are counted, more integrated, and it looks like a product
rather than a dev board on a carrier — which matters behind a clear case at $119.
Move to it for Rev B if the volume justifies the extra layout.

The shared 90% is written once. Every CSV carries a `variant` column of `common`,
`xiao` or `wroom`, and the effective design is the common rows plus one variant's.
Both are checked independently by the build, because a shared circuit with one
checked half has an unchecked half.

## Files

| | |
|---|---|
| [`netlist.csv`](netlist.csv) | Every net and its member pins, per variant. **Checked against the firmware** |
| [`placement.csv`](placement.csv) | X/Y/rotation for every part, board-local mm, with the reason it sits there |
| [`bom.csv`](bom.csv) | Per-variant, each line tagged `spec`, `class` or `estimate`, each with a KiCad footprint |
| [`xiao-pinmap.csv`](xiao-pinmap.csv) | XIAO pad → GPIO, with a source and a confirmed/unverified flag per row |
| [`outline.dxf`](outline.dxf) | 40 × 40 mm, 2 mm corner radii, mm units. Import as `Edge.Cuts` |
| [`fab.md`](fab.md) | What to select when ordering, and why |

`spec` means a real part number whose datasheet outline is settled. `class` means
the envelope is right and the SKU is still open. Same convention the project's
README uses for measurements: an unverified claim says so.

## The build checks this against the firmware

| Net | `-xiao` | `-wroom` | Firmware |
|---|---|---|---|
| `CTX` | `U3.D1` | `U3.IO2` | `PIN_CAN_TX = GPIO_NUM_2` |
| `CRX` | `U3.D2` | `U3.IO3` | `PIN_CAN_RX = GPIO_NUM_3` |
| LED | *none — the module's* | `LED_K` → `U3.IO21` | `LED_PIN`, **active low** |

`firmware/test/hardware.mjs` reads the pin number out of the sketch and checks
the netlist against **that**, translating through `xiao-pinmap.csv` on the XIAO
variant where the pad is called `D1` rather than `IO2`. Asserting "the netlist
says IO2" and "the firmware says GPIO2" as two independent facts would pass
happily after someone changed both to different values.

The bus is **500 kbit** ISO 15765-4, CAN 11-bit — what the firmware configures,
and what picks both the transceiver and the common-mode choke. The build checks
that number against the sketch too.

Two things this catches that are easy to get wrong. The LED is driven **active
low**, so on `-wroom` its anode sits on the rail through R1; flip the firmware and
that board is wrong in a way reflashing cannot fix. And on `-xiao` there must be
**no** board LED, because GPIO21 is not on a XIAO pad at all — it is the module's
own onboard LED, which is what `LED_BUILTIN 21` has always referred to. Adding one
would put two things on one pin.

## Two rules decided the layout

1. **The 12 V chain owns the left half and never crosses the CAN pair.** Power
   enters front-left and stays there; CAN H and CAN L enter front-right and reach
   U1 in about 9 mm. The switching node between U2 and L1 is the shortest, widest
   trace on the board. This is also what makes the board routable without
   crossings.
2. **The module sits at the rear with nothing underneath it.** The common parts
   are positioned to clear *both* module footprints, so the power and CAN sections
   do not move between variants.

The case picked the board size: every end cap and connector in the Minitools
modular OBD family is a **43 × 21 mm module**, so that interface is the hard
constraint and the board can be at most about 41 mm across.

## Open questions

Unresolved, not overlooked.

- **Does the case ship in clear polycarbonate at this size?** The PC variants
  verifiable in stock listings are the narrower `-N-PC` and `-L-PC` boxes, not the
  48 mm-wide `-M` this board needs. The answer changes the outline, so it comes
  before the layout.
### Answered

- **Is the XIAO's 5V pad diode-isolated from VBUS? No — it is not.** Seeed's own
  expansion-board guidance is explicit that an external supply into the 5V pad
  needs a series Schottky, anode to the supply. Without it, plugging USB in
  back-powers whatever is feeding that pad. **D5 exists because of this**, and it
  is not optional. It costs ~0.3 V, leaving ~4.7 V into the module, which its
  regulator handles comfortably.
- **Does the XIAO's regulator have headroom for U1's ~70 mA?** Not published for
  the S3. The C3's 3V3 pad is rated 700 mA and the S3 schematic names the part
  `SGM6029CYG`, but I will not plan against a rating I cannot source. Resolved by
  design instead: **R13** links the module's 3V3 to U1 on Rev A, and **U5** is an
  unpopulated local LDO on the same net. Fit one or the other, never both. Then
  measure it in Phase 1, which is already the first hardware action. An
  unpopulated footprint costs nothing next to a board spin.
- **GPIO3 is an ESP32-S3 strapping pin** (JTAG source select), driven here by
  U1's receive output, which idles high because recessive is the bus's resting
  state. Almost certainly fine, and exactly the kind of "almost certainly" that
  costs a board spin. Affects both variants.
- **L1's value** is 33–47 µH pending the LM5164 application circuit, and its
  height sets the minimum internal clearance — the part most likely to force the
  case taller.
- **R10/R11 and R12 values** — the feedback divider ratio differs by variant
  because the output does, and R12 sets the switching frequency. Both come off the
  datasheet.
- **`-wroom` only: the USB-only rail sits near 3.05 V** after D3's drop, just
  inside the ESP32-S3's 3.0–3.6 V range. Matters for bench flashing with no car
  attached; a power-mux IC is the better answer than a bigger diode.
- **Most of `xiao-pinmap.csv` is `unverified`** — the pad order comes from the
  XIAO form factor, and only D1, D2, 3V3 and GND are corroborated by this repo.
  Getting it wrong swaps pins, so check it against Seeed's own footprint before
  sending Gerbers.

## Building the board

[`build_board.py`](build_board.py) turns these CSVs into a real `.kicad_pcb`:
footprints loaded from the stock libraries, placed per `placement.csv`, nets
assigned per `netlist.csv`, and the 40 × 40 mm outline drawn on `Edge.Cuts`. Run
it with KiCad's own Python, which is the one that has `pcbnew`:

```
"%LOCALAPPDATA%\Programs\KiCad\10.0\bin\python.exe" build_board.py xiao wroom
```

Current state — both variants build with **every pad resolved**:

| | `-xiao` | `-wroom` |
|---|---|---|
| Footprints placed | 36 | 46 |
| Pads connected | 83 | 137 |
| Nets | 23 | 30 |
| Unresolved | 0 | 0 |
| Copper past the outline | none | none |

The script holds no design data of its own except the **pin name → pad number**
maps, which cannot live in the CSVs: the CSVs name pins, footprints number pads.
Those maps come from KiCad's own symbol libraries, read out by `pinout.py`, plus
`xiao-pinmap.csv` for the XIAO row order and the USB-C Type-C contact
designations for J2.

Then to look at it or export it:

```
kicad-cli pcb export glb    --output revA-xiao.glb obdurate-revA-xiao.kicad_pcb
kicad-cli pcb render        --output iso.png --quality high --perspective \
                            --zoom 0.75 --rotate "-32,0,22" obdurate-revA-xiao.kicad_pcb
kicad-cli pcb export gerbers --output gerbers/ obdurate-revA-xiao.kicad_pcb
```

GLB and PNG outputs are gitignored — they regenerate in about a second and a
quarter respectively, and there is no reason to carry megabytes of binary that a
command reproduces.

**Two things the render exposed that nothing else would have.** Stock footprints
ship their 3D models with `(hide yes)`, so the first render came out as bare pads
with no parts on it at all. And KiCad ships **no 3D model for any XIAO board** —
`MCU_Seeed_ESP32C3.step` is referenced but absent — so the `-xiao` render shows
the land pattern with nothing standing on it. The WROOM's model does exist.

**What still needs doing:** the silkscreen designators collide in the power
section, which is cosmetic but ugly and worth fixing before Gerbers. Netclasses,
the ground pour and the `-wroom` keepout zone are not created yet. And nothing is
routed — the board has a correct netlist and a ratsnest, which is the input to
routing rather than its output.

## Getting from here to Gerbers

1. Netclasses per `netlist.csv`, ground pour on an inner layer, keepout on `-wroom`.
2. Route. The layout was designed so the nets do not need to cross.
3. DRC, then `kicad-cli pcb export gerbers`.

DRC checks geometry, not whether the circuit is right. The netlist is checked
against the firmware for the CAN pins and the LED, and against itself for
completeness — but nothing checks that R8/R9 are on the correct side of U2's
EN/UVLO pin. That comes off the datasheet, which is why U2's pins are named here
rather than numbered.

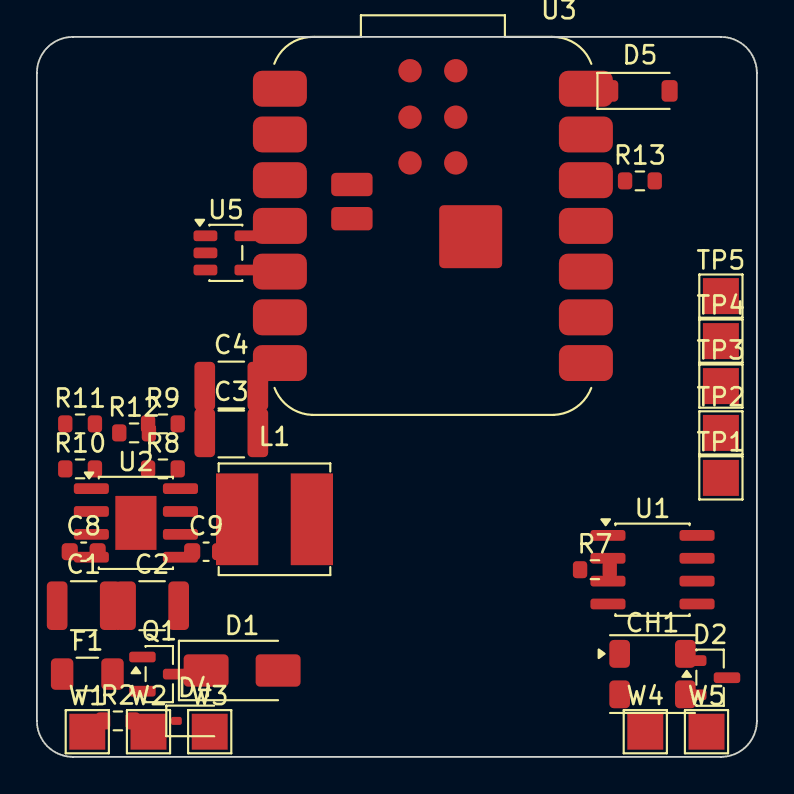
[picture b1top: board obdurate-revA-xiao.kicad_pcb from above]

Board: 4 copper layers, 40.0 x 40.0 mm, 36 parts (0 on the bottom side), 21 nets, no tracks yet.

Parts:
C1, C2: 2.2 uF 100 V; C_1210_3225Metric
C3, C4: 22 uF; C_1210_3225Metric
C8: 0.1 uF 100 V; C_0603_1608Metric
C9: 0.1 uF bootstrap; C_0603_1608Metric
CH1: CAN common-mode choke; L_CommonModeChoke_Coilank_ACM4532
D1: SMAJ33A; D_SMA
D2: NUP2105L; SOT-23
D4: 15 V zener; D_SOD-323
D5: Schottky 1 A; D_SOD-123
F1: polyfuse 500 mA; Fuse_1206_3216Metric
L1: 33 uH inductor; L_Bourns_SRN6045TA
Q1: P-ch MOSFET; SOT-23
R2: 100 k; R_0603_1608Metric
R7: 0 ohm; R_0603_1608Metric
R8: EN/UVLO upper; R_0603_1608Metric
R9: EN/UVLO lower; R_0603_1608Metric
R10: FB upper; R_0603_1608Metric
R11: FB lower; R_0603_1608Metric
R12: RON; R_0603_1608Metric
R13: 0 ohm link; R_0603_1608Metric
TP1: test pad 12V; TestPoint_Pad_2.0x2.0mm
TP2: test pad CANH; TestPoint_Pad_2.0x2.0mm
TP3: test pad CANL; TestPoint_Pad_2.0x2.0mm
TP4: test pad 3V3; TestPoint_Pad_2.0x2.0mm
TP5: test pad GND; TestPoint_Pad_2.0x2.0mm
U1: SN65HVD230DR; SOIC-8_3.9x4.9mm_P1.27mm
U2: LM5164-Q1; SOIC-8-1EP_3.9x4.9mm_P1.27mm_EP2.29x3mm
U3: XIAO ESP32S3; MCU_Seeed_ESP32C3
U5: AP2112K-3.3 (DNP); SOT-23-5
W1: wire pad V_BATT; TestPoint_Pad_2.0x2.0mm
W2, W3: wire pad GND; TestPoint_Pad_2.0x2.0mm
W4: wire pad CAN_H; TestPoint_Pad_2.0x2.0mm
W5: wire pad CAN_L; TestPoint_Pad_2.0x2.0mm

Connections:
3V3: R13.2, TP4.1, U1.3, U5.5
BST: C9.1, U2.7
CAN_H: CH1.1, D2.1, TP2.1, W4.1
CAN_H_F: CH1.2, U1.7
CAN_L: CH1.3, D2.3, TP3.1, W5.1
CAN_L_F: CH1.4, U1.6
CRX: U1.4, U3.3
CTX: U1.1, U3.2
FB: R10.2, R11.1, U2.5
GND: C1.2, C2.2, C3.2, C4.2, C8.2, D1.2, D2.2, R2.2, R7.2, R9.2, R11.2, R12.2, TP5.1, U1.2, U2.1, U2.9, U3.13, U5.2, W2.1, W3.1
RON: R12.1, U2.4
RS: R7.1, U1.8
SW: C9.2, L1.1, U2.8
UVLO: R8.2, R9.1, U2.3
V5: D5.1, U3.14, U5.1
VF: D4.1, F1.2, Q1.2
VGATE: D4.2, Q1.1, R2.1
VOUT: C3.1, C4.1, D5.2, L1.2, R10.1
V_BATT: F1.1, TP1.1, W1.1
V_IN: C1.1, C2.1, C8.1, D1.1, Q1.3, R8.1, U2.2
XIAO_3V3: R13.1, U3.12
